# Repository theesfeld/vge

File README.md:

# MFD — multi-function display library

<!-- agents:status:begin -->
> **Status:** active · `0.1.0-dev.1` · **vehicle CMFD** · format select · drive capture · display-only · [#103](https://github.com/theesfeld/mfd/issues/103) · MIT
<!-- agents:status:end -->

## What this is

Composable **instrument pages** for:

- F-16-class **jet MFD formats** (SMS, HSD, TGP, FCR, ENG, FUEL, …)
- **Automotive** cluster / OBD pages reusing the same widgets
- A **plug-in bezel** (20 OSB + knobs) so keyboard POC and real GPIO share one path

**Face geometry:** F-16 MLU color MFD ≈ **4×4 in (10×10 cm)**. The demo sizes the face like a **ruler on your monitor**: `side_px = 4" × display_PPI` (EDID or `MFD_PPI`), then maps a **visually square** cell box so it is not stretched.

**Text:** baked **B612 Mono** atlas (no runtime TTF).  
**Draw core:** pure asm **libmfd** (`mfd_plot` / `mfd_line` / …).

## Docs (start here)

| Doc | Contents |
|-----|----------|
| **[docs/API.md](docs/API.md)** | Full API/ABI white paper |
| **[docs/widgets.md](docs/widgets.md)** | Widget list + ASCII diagrams |
| **[docs/reference/f16-mfd-catalog.md](docs/reference/f16-mfd-catalog.md)** | Formats, OSB map, public manual sources |
| **[docs/reference/mfd-photo-index.md](docs/reference/mfd-photo-index.md)** | Public photo search index |

## Drive day (one command)

```bash
cd ~/Projects/mfd
./cmfd.sh
```

Release build + live vehicle CMFD + **crush OBD/UDS capture** under `captures/drive-TIMESTAMP/`.  
Quit with Esc. After the commute, parse that directory.

| Mode | Command |
|------|---------|
| Drive (default) | `./cmfd.sh` |
| Headless maximal capture | `./cmfd.sh capture --seconds 7200` |
| Glass only | `./cmfd.sh glass` |

Full notes: **[docs/drive-day.md](docs/drive-day.md)**.

## Build and run (live glass)

```bash
cd ~/Projects/mfd
make
./cmfd.sh                 # drive: release + BT + capture
cargo run --release --bin cmfd
# Ghostty/Kitty:
MFD_TERM=kitty cargo run --release --bin cmfd
```

Default: **vehicle CMFD** (ENG bank), **30 Hz**. **No SIM** — until OBD is live, glass shows empty data and SEARCH/RECONN.

### Auto pages (default) — jump keys

| Key | Page | Content |
|-----|------|---------|
| `1` | CLUSTER | RPM, speed, gear, throttle |
| `2` | FUEL | Fuel / battery / load **tapes** |
| `3` | TEMPS | Oil, coolant, trans, IAT, MAF, EGT |
| `4` | DRIVE | P/R/N/D/M · 2H/4H/4L |
| `5` | LIGHTS | Beams, fog, brake, turns, cabin |
| `6` | TPM | Four tire pressures |
| `7` | BODY | Doors + seat belts |
| `8` | CLIMATE | Out/in temp, HVAC |
| `9` | **FLIR** | Camera / FLIR glass |
| `0` | **RANGE** | Collision / park arcs |
| `v` | **ATT** | Horizon sphere + heading ° / N–NW |
| `x` | **MAP** | Schematic topo (demo scroll) |
| `f` | **DTC** | All fault codes (read only · Mode 03/07/0A) |
| `o` / `s` | OBD / SETUP | PIDs · config |
| `n` / `p` | Next / previous page | |
| `[` `]` | **BRT** −/+ (real CMFD rocker) | |
| `u` | Speed unit | MPH → KM/H → KT |
| `a` / `j` / Tab | Auto / Jet / toggle | |

OSB (auto): top CLST…LITE · right TPM/BODY/CLIM/FLIR/**RNG** · left OBD/SET/**ATT**/**MAP**.

### Sensors (env)

| Env | Role |
|-----|------|
| `MFD_CAMERA=/dev/video0` or `auto` | Live V4L2 → FLIR |
| `MFD_FLIR_PATH=grey.pgm` | Still greyscale |
| `MFD_OBD_BT` / `MFD_OBD_PORT` / `MFD_OBD_REPLAY` | Live OBD (native stack). BT **keeps searching/reconnecting** until up |
| `MFD_OBD_CAPTURE=dir` | Log frames/signals while glass runs (one BT client) |
| `MFD_OBD_CAPTURE_FULL=1` | Log every TX/RX + every signal (heavy; long drives bog the host) |
| `MFD_OBD_CRUSH=1` | Discover all Mode 01 PIDs + multi-module UDS |
| `MFD_RANGE=2.1,3,2.8,1.2` | Range page (m) |
| `MFD_AUTO_PAGE=FLIR` | Start page |

See `docs/auto-sensors.md` and **`docs/hardware.md`** (physical 4×4 + OSB; prefer vehicle bus for pitch/heading).  
Jet: `m` Master Menu · `g` widget QA · OSB 12/13/14.  
MLU M1 CMFD SoT: `docs/reference/mlu-m1-cmfd.md`.

### Bezel knobs (when not using page jump keys)

| Key | Event |
|-----|--------|
| `q w e r t` | Bottom OSB 15–11 |
| `a s d f g` | Left OSB (on jet; on auto `a`=`AUTO`, `s`=`SETUP`) |
| `; '` | Contrast −/+ |
| `- =` | Symbology −/+ |
| `, .` | Gain −/+ |
| `c` | Color mode |
| `Esc` | Quit |

## Quick model

```text
BezelSource ──BezelEvent──► BezelState
                              │
                         app loop routes OSB
                              │
              ┌───────────────┴───────────────┐
              ▼                               ▼
        jet::draw_format               auto::draw_auto
              │                               │
              └──────── widgets + font ───────┘
                              │
                         Surface (square)
                              │
                    apply_brightness(BRT)
                              │
                    term present (PresentScratch)
```

```rust
use mfd::{
    auto, bezel, jet, page::Page, palette::{ColorMode, Palette}, Surface,
};

let mut s = Surface::new(512, 512);
let mut page = Page::new(&mut s);
let pal = Palette::new(ColorMode::ColorMfd);
let st = bezel::BezelState::default();
jet::draw_format(&mut page, jet::Format::Eng, &pal, &st, 0.0);
s.apply_brightness(st.brightness);
```

## Widget list (summary)

Full diagrams: **[docs/widgets.md](docs/widgets.md)**

`bezel_frame` · `osb_chrome` · `content_after_osb` · `softkey_row` · **`tape_gauge`** · **`round_gauge`** · `label` · `range_rings` · `bearing_pointer` · `track_gate` · `crosshair` · `bscope_grid` · `list_menu` · `station_grid` · `numeric_readout` · `caution_box` · `horizon_cue` · `progress_strip` · `video_frame`

**See all widgets:** demo starts on **WIDG** gallery (`g` key or left OSB **WIDG**). Other formats: bottom OSB **FUEL** / **ENG**, top bank for SMS/HSD/…

## Jet formats

`BLANK WIDG SMS HSD TGP FCR FCR-GM FCR-SEA WPN HAD FLIR DTE TEST ENG FUEL CNI RESET ECM TFR HUD UFC PFL STORES`

## Auto formats

`CLUSTER POWER TEMPS OBD SETUP` + `ObdSnapshot` (normalize OBD PIDs at the edge).

## Color modes

| Mode | Role |
|------|------|
| `GreenMono` | Classic green |
| `ColorMfd` | Color LCD palette |
| `HighVis` | Yellow-dominant |

## Face size (ruler-accurate 4×4 on any screen)

Default face is **4.0 inches square** on the **physical monitor** (F-16 MLU class).

```
side_px = MFD_FACE_IN × PPI
viewport cells chosen so on-glass width = height = side
```

| Env | Meaning |
|-----|---------|
| `MFD_FACE_IN=4` | Edge length in **inches** (default **4**) |
| `MFD_PPI=190` | **Force** pixels/inch (use if EDID is wrong — put a ruler on the panel) |
| `MFD_PX_SCALE=0.76` | **Force** device_px per terminal winsize px (use if the face is still wrong) |
| `MFD_MAX_W` / `MFD_MAX_H` | Cap FB (default **1024**) |

PPI detection: `MFD_PPI` → EDID detailed mm → EDID cm → 96 (not accurate).

**Pixel space:** EDID PPI is panel **device** pixels. Ghostty `TIOCGWINSZ` is often **buffer** pixels at a different content scale than the compositor (e.g. content ~2, niri scale 1.5). The layout converts winsize cells to device pixels via the compositor window size when available (`niri` / `hyprctl` / `swaymsg`), or `MFD_PX_SCALE`.

Startup example:
```text
ruler face 4.00" @ 191.2 ppi (EDID-cm)  px×0.763 (compositor)  cell 14.5×32.1dev  → 765×765px  cells 53×24  on-glass 4.00"×4.00"
```
If the terminal is too small: `on-glass` drops and `[clipped to window]` is printed.

## Performance notes

- Long crawls: huge Kitty payloads — demo uses capped square face, **30 Hz**, **PresentScratch**.  
- Rate: `MFD_HZ=60` if the terminal keeps up.

## License

- Code: **MIT**  
- B612 + atlas: **EPL-2.0** — `NOTICE`, `assets/fonts/`

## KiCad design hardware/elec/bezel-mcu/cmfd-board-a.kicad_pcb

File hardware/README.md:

# CMFD hardware platform

**Start here if you do not use KiCad:** [`ORDER-THIS.md`](ORDER-THIS.md)

**Issue:** [#137](https://github.com/theesfeld/mfd/issues/137)  
**Class:** Universal color multi-function display (F-16 CMFD *spirit* + late-80s industrial skin)  
**Not:** flight-certified equipment · not an OEM F-16 LRU · not a single-board computer in a shell

## What you get

| Path | Contents |
|------|----------|
| [`elec/bezel-mcu/`](elec/bezel-mcu/) | Board A — bezel / matrix / sensors MCU |
| [`elec/carrier-som/`](elec/carrier-som/) | Board B — Linux SoM carrier, power, ports |
| [`elec/fab/`](elec/fab/) | **Gerber + drill + BOM + CPL** ready for JLCPCB / PCBWay |
| [`mech/print/`](mech/print/) | **STL** files for 3D print houses |
| [`mech/src/`](mech/src/) | OpenSCAD sources (regenerate STLs) |
| [`bom/`](bom/) | Master BOM (full + lean ≤$300 config) |
| [`viewer/`](viewer/) | Three.js interactive **exploded view** |
| [`../docs/hardware/`](../docs/hardware/) | Requirements, connector ICD, power, flash |

## Quick send-out

### PCB fab (both boards) — KiCad headless (preferred)

1. Upload `elec/fab/cmfd-board-a-kicad-gerbers.zip` and `elec/fab/cmfd-board-b-kicad-gerbers.zip`.
2. Order **2-layer**, 1.6 mm, HASL or ENIG.
3. Open boards in KiCad 10: `elec/bezel-mcu/cmfd-board-a.kicad_pcb`, `elec/carrier-som/cmfd-board-b.kicad_pcb`.
4. Read DRC notes: `elec/fab/SEND-TO-FAB.md`.

```bash
# rebuild .kicad_pcb + DRC + Gerbers/drill/pos
nix-shell -p kicad zip --run 'bash hardware/tools/kicad_export.sh'
```

Legacy geometry-only Gerbers: `python3 hardware/tools/gen_pcbs.py` (prefer KiCad zips for fab).

### 3D print

Send all `mech/print/*.stl` (or the combined zip). Recommended:

| Part | Material | Notes |
|------|----------|--------|
| `cmfd-front-bezel.stl` | PETG or ABS | Face; 0.2 mm layers |
| `cmfd-rear-shell.stl` | PETG or ABS | Ports + tray |
| `cmfd-battery-tray.stl` | PETG | 18650 retention |
| `cmfd-osb-cap.stl` ×20 | PETG | Print 20 copies |
| `cmfd-rocker.stl` ×4 | PETG | Print 4 copies |
| `cmfd-corner-bumper.stl` ×4 | **TPU 95A** | Drop protection |

```bash
nix-shell -p openscad --run 'bash hardware/tools/export_stls.sh'
```

### Exploded view

Open `hardware/viewer/index.html` in a browser (or the copy under `site/hardware/`).

## Architecture (two board)

```
Face (print)  →  Board A (MCU, OSB matrix, sensors)
                     │ board-to-board
Display glass ←  Board B (SoM, graphics, power, ports, RF)
                     │
                 18650 tray + USB-C charge
```

Operator I/O law (software SoT): [`docs/hardware-bezel.md`](../docs/hardware-bezel.md).

## Safety

Display-only when used as vehicle glass: **no** bus-write actuators on either board. CAN is isolated transceiver only.

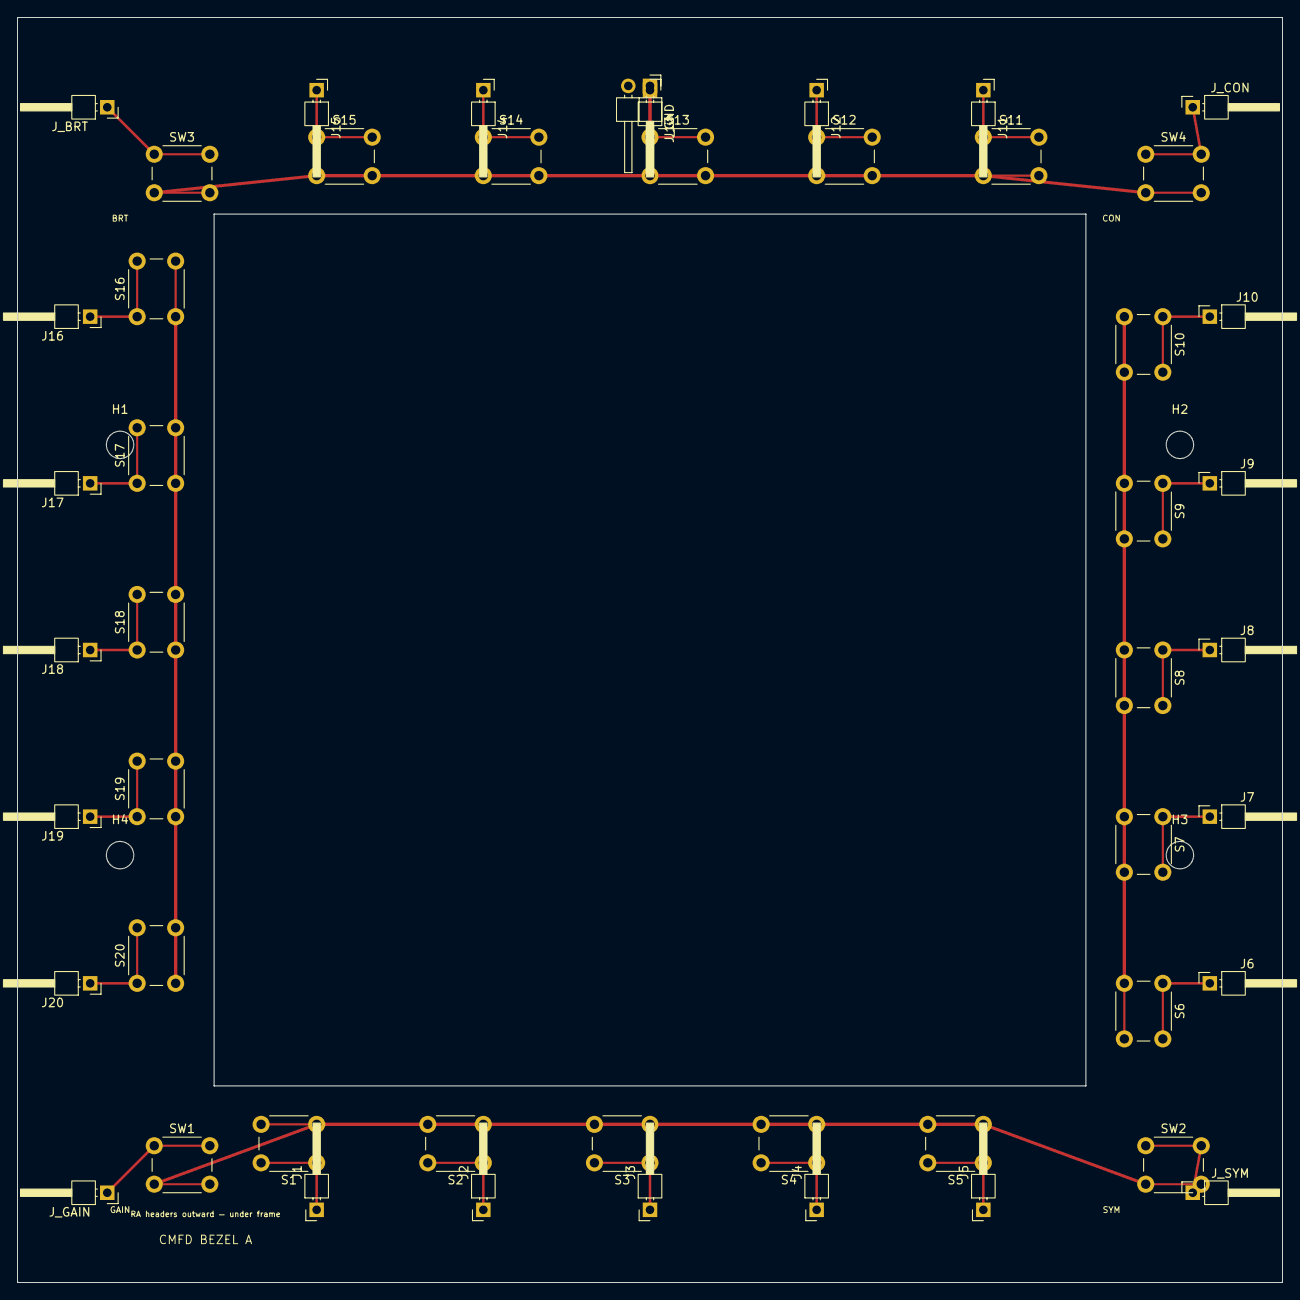
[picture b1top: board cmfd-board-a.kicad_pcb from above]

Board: 2 copper layers, 148.0 x 148.0 mm, 53 parts (0 on the bottom side), 25 nets.

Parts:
H1, H2, H3, H4: M3; MountingHole_3.2mm_M3
J1: OSB1; PinHeader_1x01_P2.54mm_Horizontal
J2: OSB2; PinHeader_1x01_P2.54mm_Horizontal
J3: OSB3; PinHeader_1x01_P2.54mm_Horizontal
J4: OSB4; PinHeader_1x01_P2.54mm_Horizontal
J5: OSB5; PinHeader_1x01_P2.54mm_Horizontal
J6: OSB6; PinHeader_1x01_P2.54mm_Horizontal
J7: OSB7; PinHeader_1x01_P2.54mm_Horizontal
J8: OSB8; PinHeader_1x01_P2.54mm_Horizontal
J9: OSB9; PinHeader_1x01_P2.54mm_Horizontal
J10: OSB10; PinHeader_1x01_P2.54mm_Horizontal
J11: OSB11; PinHeader_1x01_P2.54mm_Horizontal
J12: OSB12; PinHeader_1x01_P2.54mm_Horizontal
J13: OSB13; PinHeader_1x01_P2.54mm_Horizontal
J14: OSB14; PinHeader_1x01_P2.54mm_Horizontal
J15: OSB15; PinHeader_1x01_P2.54mm_Horizontal
J16: OSB16; PinHeader_1x01_P2.54mm_Horizontal
J17: OSB17; PinHeader_1x01_P2.54mm_Horizontal
J18: OSB18; PinHeader_1x01_P2.54mm_Horizontal
J19: OSB19; PinHeader_1x01_P2.54mm_Horizontal
J20: OSB20; PinHeader_1x01_P2.54mm_Horizontal
J_BRT: BRT; PinHeader_1x01_P2.54mm_Horizontal
J_CON: CON; PinHeader_1x01_P2.54mm_Horizontal
J_GAIN: GAIN; PinHeader_1x01_P2.54mm_Horizontal
J_GND: GND; PinHeader_1x02_P2.54mm_Horizontal
J_SYM: SYM; PinHeader_1x01_P2.54mm_Horizontal
S1: OSB1; SW_PUSH_6mm_H4.3mm
S2: OSB2; SW_PUSH_6mm_H4.3mm
S3: OSB3; SW_PUSH_6mm_H4.3mm
S4: OSB4; SW_PUSH_6mm_H4.3mm
S5: OSB5; SW_PUSH_6mm_H4.3mm
S6: OSB6; SW_PUSH_6mm_H4.3mm
S7: OSB7; SW_PUSH_6mm_H4.3mm
S8: OSB8; SW_PUSH_6mm_H4.3mm
S9: OSB9; SW_PUSH_6mm_H4.3mm
S10: OSB10; SW_PUSH_6mm_H4.3mm
S11: OSB11; SW_PUSH_6mm_H4.3mm
S12: OSB12; SW_PUSH_6mm_H4.3mm
S13: OSB13; SW_PUSH_6mm_H4.3mm
S14: OSB14; SW_PUSH_6mm_H4.3mm
S15: OSB15; SW_PUSH_6mm_H4.3mm
S16: OSB16; SW_PUSH_6mm_H4.3mm
S17: OSB17; SW_PUSH_6mm_H4.3mm
S18: OSB18; SW_PUSH_6mm_H4.3mm
S19: OSB19; SW_PUSH_6mm_H4.3mm
S20: OSB20; SW_PUSH_6mm_H4.3mm
SW1: GAIN; SW_PUSH_6mm_H4.3mm
SW2: SYM; SW_PUSH_6mm_H4.3mm
SW3: BRT; SW_PUSH_6mm_H4.3mm
SW4: CON; SW_PUSH_6mm_H4.3mm

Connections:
GND: J_GND.1, J_GND.2, S1.2, S2.2, S3.2, S4.2, S5.2, S6.2, S7.2, S8.2, S9.2, S10.2, S11.2, S12.2, S13.2, S14.2, S15.2, S16.2, S17.2, S18.2, S19.2, S20.2, SW1.2, SW2.2, SW3.2, SW4.2
OSB1: J1.1, S1.1
OSB2: J2.1, S2.1
OSB3: J3.1, S3.1
OSB4: J4.1, S4.1
OSB5: J5.1, S5.1
OSB6: J6.1, S6.1
OSB7: J7.1, S7.1
OSB8: J8.1, S8.1
OSB9: J9.1, S9.1
OSB10: J10.1, S10.1
OSB11: J11.1, S11.1
OSB12: J12.1, S12.1
OSB13: J13.1, S13.1
OSB14: J14.1, S14.1
OSB15: J15.1, S15.1
OSB16: J16.1, S16.1
OSB17: J17.1, S17.1
OSB18: J18.1, S18.1
OSB19: J19.1, S19.1
OSB20: J20.1, S20.1
RK_BRT: J_BRT.1, SW3.1
RK_CON: J_CON.1, SW4.1
RK_GAIN: J_GAIN.1, SW1.1
RK_SYM: J_SYM.1, SW2.1

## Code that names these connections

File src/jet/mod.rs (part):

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    (
        ["BLANK", "HAD", "", "RCCE", "RSET"],
        ["SMS", "HSD", "DTE", "TEST", "FLCS"],
        // L→R: OSB15 SWAP, OSB14 (pri label), OSB13 (sec), OSB12 (ter), OSB11 DCLT
        ["SWAP", "FCR", "HSD", "SMS", "DCLT"],
        // top→bot OSB20..16: FCR TGP WPN TFR FLIR
        ["FCR", "TGP", "WPN", "TFR", "FLIR"],
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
